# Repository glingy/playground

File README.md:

# Atmel SAM D21 Playground!

## Important Links
 * Documentation: WIP
 * How to make your own Playground: [docs/making_a_playground.md](./docs/making_a_playground.md)
 * BOM: https://playground.ctrtl.com/bom
 * Schematic: https://playground.ctrtl.com/schematic.pdf
 * ATSAMD21E15L Datasheet: https://playground.ctrtl.com/SAMD21.pdf
 * Latest Gerber Files: https://github.com/glingy/playground/releases/latest

This repository contains the development kit for building code for the Atmel SAM D21 playground board. This board was developed to help members of the Solar Car Club (Prisum) at Iowa State University to learn how to program very low level embedded code. This repository is a reduced version of the development environment used by the team.

### Getting Started
 - Download VS Code (https://code.visualstudio.com)
 - Install Git (`build-essential` package on Ubuntu, Run `xcode-select --install` in a terminal on macOS, or install from https://git-scm.com/downloads for Windows)
 - Clone this repository to your computer
 - Open the folder with VS Code (Either drag the folder onto the VS Code application or open VS Code and select `Open Folder...`)
 - VS Code will prompt you to install some recommended extensions. Do so, it should install PlatformIO, C/C++ tools, multisrc, and Explorer Exclude.
   - This environment is based on PlatformIO (https://platformio.org) with several modifications to make it easier to use.

### What is all this stuff?
 - Several of these are hidden by default, look in the `Hidden Items` tab in the explorer sidebar to see them. If it's hidden, you can ignore it for the most part.
 - `.vscode` - VSCode configuration. Suggested extensions, file type associations, configuration of what's hidden, etc.
 - `boards` - PlatformIO board definition for the playground board.
 - `include` - Shared header files across all projects (See PlatformIO documentation)
 - `lib` - Shared library code across all projects (See PlatformIO documentation)
 - `scripts` - Linker scripts and C startup files. You probably won't need to touch this, but feel free to explore
 - `sources` - The code folder! To create a new project, create a new folder in here. To be detected as a valid project, it must contain at least once `.c` file.
 - `.clang-format` - Auto-formatter config file. It's who you blame if your code magically reorganizes whenever you save the file.
 - `.gitignore` - Tells git to ignore specific files which should not be tracked.
 - `.multisrc` - Tells the multisrc extension to activate and allow you to select source folders.
 - `README.md` - This file!
 - `platformio.ini` - PlatformIO config file.
 - `multisrc.ini` - Generated PlatformIO config file by multisrc

### Bottom Status Bar Overview
PlatformIO adds a lot of buttons to the bottom status bar in VSCode. From left to right:
 - The first button is the checkmark, clicking that will build your code, but not run it. Good for checking syntax or verifying code when you don't have a board with you to run it on.
 - The second is the right arrow, that's the run button. It will build and run your code using the selected debugger.
 - The third is the trash can, that will delete everything from the build folder. If there's a strange linker error for some reason, you can try cleaning, but I've found that it's usually your fault and not because the build folder is dirty.
 - The serial monitor (plug) is not used yet.
 - The terminal will open a local terminal window with the `pio` command set up for debugging the development environment.
 - The next is the selected debugger. By default, it will assume the playground's internal debugger, but you can select another in `local.ini`. See `platform.ini` for example debugger definitions.
 - When editing, you may see a database icon and/or a fire symbol to the left of the line and column numbers. That indicates that intellisense is parsing the file, so if syntax highlighting or linting looks broken, wait for those to disappear, and if it's not fixed by the time they disappear, close and reopen the file.
 - In the bottom right corner of VSCode, `< something >` indicates the source folder currently selected for running / debugging. It will be red if you're looking at a file not in the current project so you don't compile the wrong project on accident. Click that to select a different project

### Running
 - Select the program. Select the debugger. Press the arrow.

### Debugging
 - On the left sidebar, there's a bug with a play button, press the green arrow at the top of that sidebar to debug.
   - `Variables` are the global (and local) variables that were not optimized away. You can also hover over a variable to see its value. If it says `<optimized away>`, the compiler decided that variable wasn't worth keeping around, so you'll have to either declare it `volatile` and re-download (forces compiler to not optimize it out; remove `volatile` when done) or look around to find its value from nearby functions or calculations.
   - `Watch` lets you type C expressions and see the results. This is extremely useful also for optimized math, you can put any simple C expression (including math) in there, `&var` or `&var + len` is often useful for checking addresses of different things.
   - `Call Stack` shows which functions you're currently inside. If you go above `main`, you're now in the `scripts/startup.c` file. Click on an entry to jump to that function.
   - `Peripherals` shows the current status of every register in the processor. Extremely useful, especially if something's just broken and you have no idea why. Sometimes, register values won't update unless you click on them to expand them, if you see it flash or a loading bar at the top flash by, it probably just updated. Most useful part of debugging.
   - `Breakpoints` is self-explanatory. Click next to a line number to add a breakpoint. Note: Breakpoints listed there are for *all* projects, not just the current one, so it might be useful to remove breakpoints as soon as you're done with one.
   - `Registers` is not very useful for us, it's the current value of every register in the processor.
   - `Memory` enter a memory address and offset to see the hex value of that chunk of memory.
   - `Disassembly` if it works, it will disassemble a function to let you see the assembly form it is currently running. I've had issues with that in the past.
 - You can press the run button or the debug button again while debugging the program, different debuggers behave differently, some get angry, some stop the current debug process while making vscode think you're still debugging, some just ignore you. I suggest you press the stop debugging button before starting a new program.
 - The reload button will restart the current program, but *will not recompile nor re-download*. If you want to download a new version, stop and restart.

### Troubleshooting
**Help!** LED doesn't turn on!
 - Check wiring direction of external pullup/pulldown resistors (0/1)
 - Check output direction

**Help!** A peripheral isn't working!
 - Is it enabled in APB? - Did you wait after enabling it for the clock to enable?
 - Does it need AHB enabled?
 - Is it enabled?
 - Is its GCLK enabled?

**Help!** I need to force wipe and reset the board!
 - TBD

**Help!** It's just not working!
 - Yup. Welcome to software. Take a break and come back later. The answer's probably staring you in the face.

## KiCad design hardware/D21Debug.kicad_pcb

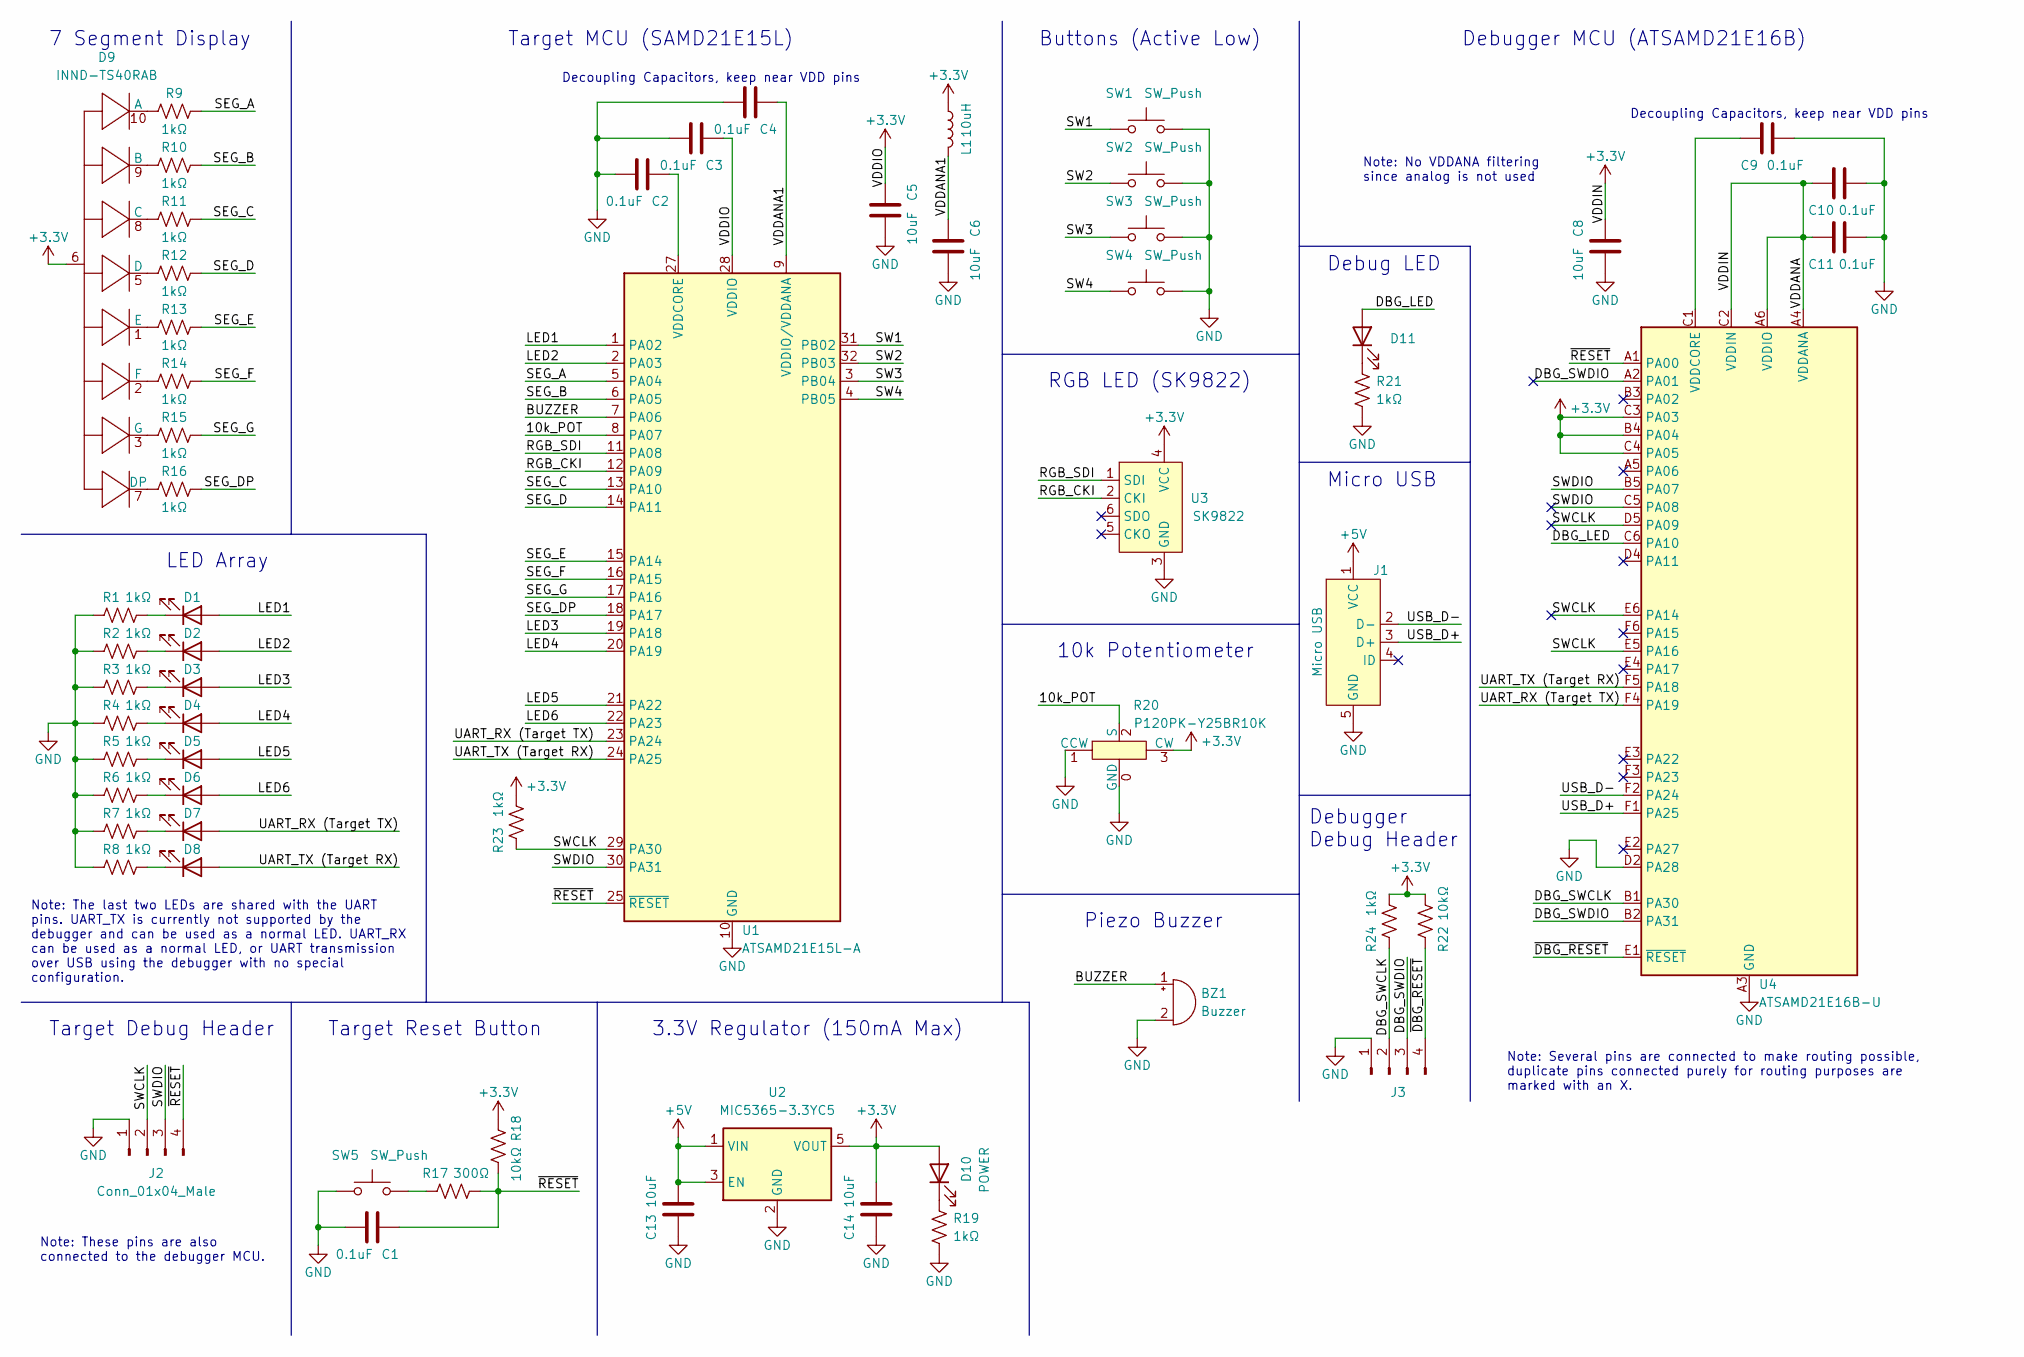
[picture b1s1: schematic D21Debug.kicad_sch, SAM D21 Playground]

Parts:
BZ1: Buzzer; PS1240P02BT
C1, C2, C3, C4, C9, C10, C11: 0.1uF; C_0603_1608Metric_Pad1.08x0.95mm_HandSolder
C5, C6, C8, C13, C14: 10uF; C_0603_1608Metric_Pad1.08x0.95mm_HandSolder
D1, D2, D3, D4, D5, D6, D7, D8, D11: LED_0603_1608Metric_Pad1.05x0.95mm_HandSolder
D9: INND-TS40RAB
D10: POWER; LED_0603_1608Metric_Pad1.05x0.95mm_HandSolder
J1: Micro USB; MCR-B-S-RA-SMT-CS5A-NF-T
J2, J3: Conn_01x04_Male; PinHeader_1x04_P2.54mm_Vertical
L1: 10uH; L_0603_1608Metric_Pad1.05x0.95mm_HandSolder
R1, R2, R3, R4, R5, R6, R7, R8, R9, R10, R11, R12, R13, R14, R15, R16, R19, R21, R23, R24: 1kΩ; R_0603_1608Metric_Pad0.98x0.95mm_HandSolder
R17: 300Ω; R_0603_1608Metric_Pad0.98x0.95mm_HandSolder
R18, R22: 10kΩ; R_0603_1608Metric_Pad0.98x0.95mm_HandSolder
R20: P120PK-Y25BR10K
SW1, SW2, SW3, SW4, SW5: SW_Push; SW_PUSH_6mm
U1: ATSAMD21E15L-A; TQFP-32_7x7mm_P0.8mm
U2: MIC5365-3.3YC5; SOT-353_SC-70-5
U3: SK9822
U4: ATSAMD21E16B-U; WLCSP-35

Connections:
+3V3: C3.1, C5.1, C8.1, C10.1, C11.1, C14.2, D9.6, D10.2 (A), L1.2, R18.1, R20.3 (CW), R22.1, R23.2, R24.2, U1.28 (VDDIO), U2.5 (VOUT), U3.4 (VCC), U4.A4 (VDDANA), U4.A6 (VDDIO), U4.B4 (PA04), U4.C2 (VDDIN), U4.C3 (PA03), U4.C4 (PA05)
+5V: C13.2, J1.1 (VCC), U2.1 (VIN), U2.3 (EN)
/10k_POT: R20.2 (S), U1.8 (PA07)
/BUZZER: BZ1.1 (-), U1.7 (PA06)
/DBG_LED: D11.2 (A), U4.C6 (PA10)
/DBG_SWCLK: J3.2, R24.1, U4.B1 (PA30)
/DBG_SWDIO: J3.3, U4.A2 (PA01), U4.B2 (PA31)
/LED1: D1.2 (A), U1.1 (PA02)
/LED2: D2.2 (A), U1.2 (PA03)
/LED3: D3.2 (A), U1.19 (PA18)
/LED4: D4.2 (A), U1.20 (PA19)
/LED5: D5.2 (A), U1.21 (PA22)
/LED6: D6.2 (A), U1.22 (PA23)
/RGB_CKI: U1.12 (PA09), U3.2 (CKI)
/RGB_SDI: U1.11 (PA08), U3.1 (SDI)
/SEG_A: R9.2, U1.5 (PA04)
/SEG_B: R10.2, U1.6 (PA05)
/SEG_C: R11.2, U1.13 (PA10)
/SEG_D: R12.2, U1.14 (PA11)
/SEG_DP: R16.2, U1.18 (PA17)
/SEG_E: R13.2, U1.15 (PA14)
/SEG_F: R14.2, U1.16 (PA15)
/SEG_G: R15.2, U1.17 (PA16)
/SW1: SW1.1, U1.31 (PB02); also elsewhere on the board
/SW2: SW2.1, U1.32 (PB03); also elsewhere on the board
/SW3: SW3.1, U1.3 (PB04)
/SW4: SW4.1, U1.4 (PB05)
/SWCLK: J2.2, R23.1, U1.29 (PA30), U4.D5 (PA09), U4.E5 (PA16), U4.E6 (PA14)
/SWDIO: J2.3, U1.30 (PA31), U4.B5 (PA07), U4.C5 (PA08)
/UART_RX (Target TX): D7.2 (A), U1.23 (PA24), U4.F4 (PA19)
/UART_TX (Target RX): D8.2 (A), U1.24 (PA25), U4.F5 (PA18)
/USB_D+: J1.3 (D+), U4.F1 (PA25)
/USB_D-: J1.2 (D-), U4.F2 (PA24)
/VDDANA1: C4.1, C6.1, L1.1, U1.9 (VDDIO/VDDANA)
/~DBG_RESET: J3.4, R22.2, U4.E1 (~RESET)
/~RESET: C1.1, J2.4, R17.2, R18.2, U1.25 (~RESET), U4.A1 (PA00)
GND: BZ1.2 (+), C1.2, C2.2, C3.2, C4.2, C5.2, C6.2, C8.2, C9.2, C10.2, C11.2, C13.1, C14.1, J1.5 (GND), J2.1, J3.1, R1.1, R2.1, R3.1, R4.1, R5.1, R6.1, R7.1, R8.1, R19.2, R20.0 (GND), R20.1 (CCW), R21.2, SW1.2, SW2.2, SW3.2, SW4.2, SW5.1, U1.10 (GND), U1.26 (GND), U2.2 (GND), U3.3 (GND), U4.A3 (GND), U4.D2 (PA28), U4.G (GND); also elsewhere on the board
unnamed: D1.1 (K), R1.2
unnamed: D2.1 (K), R2.2
unnamed: D3.1 (K), R3.2
unnamed: D4.1 (K), R4.2
unnamed: D5.1 (K), R5.2
unnamed: D6.1 (K), R6.2
unnamed: D7.1 (K), R7.2
unnamed: D8.1 (K), R8.2
unnamed: D9.10 (A), R9.1
unnamed: D9.9 (B), R10.1
unnamed: D9.8 (C), R11.1
unnamed: D9.5 (D), R12.1
unnamed: D9.7 (DP), R16.1
unnamed: D9.1 (E), R13.1
unnamed: D9.2 (F), R14.1
unnamed: D9.3 (G), R15.1
unnamed: D10.1 (K), R19.1
unnamed: D11.1 (K), R21.1
unnamed: R17.1, SW5.2
unnamed: C2.1, U1.27 (VDDCORE)
unnamed: C9.1, U4.C1 (VDDCORE)

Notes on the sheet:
3.3V Regulator (150mA Max)
Target MCU (SAMD21E15L)
Note: The last two LEDs are shared with the UART pins. UART_TX is currently not supported by the debugger and can be used as a normal LED. UART_RX can be used as a normal LED, or UART transmission over USB using the debugger with no special configuration.
Note: Several pins are connected to make routing possible, duplicate pins connected purely for routing purposes are marked with an X.
Micro USB
Debugger MCU (ATSAMD21E16B)
Target Debug Header
Decoupling Capacitors, keep near VDD pins
Debug LED
LED Array
Piezo Buzzer
Debugger Debug Header
RGB LED (SK9822)
Note: These pins are also connected to the debugger MCU.
10k Potentiometer
Buttons (Active Low)
7 Segment Display
Target Reset Button
Note: No VDDANA filtering since analog is not used

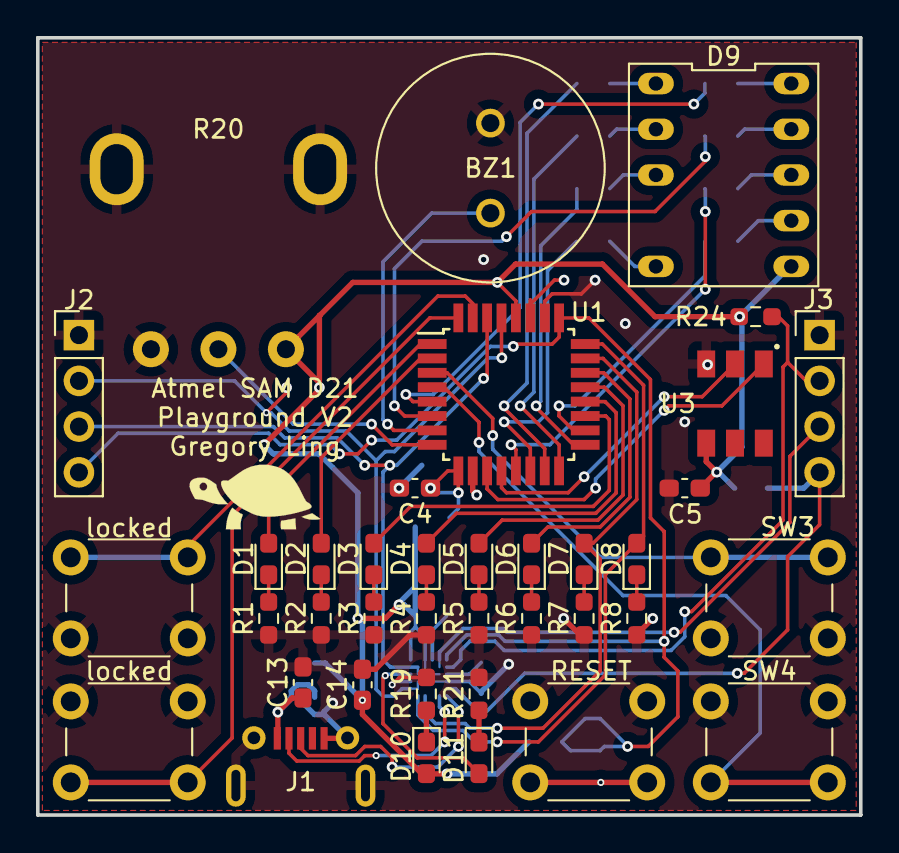
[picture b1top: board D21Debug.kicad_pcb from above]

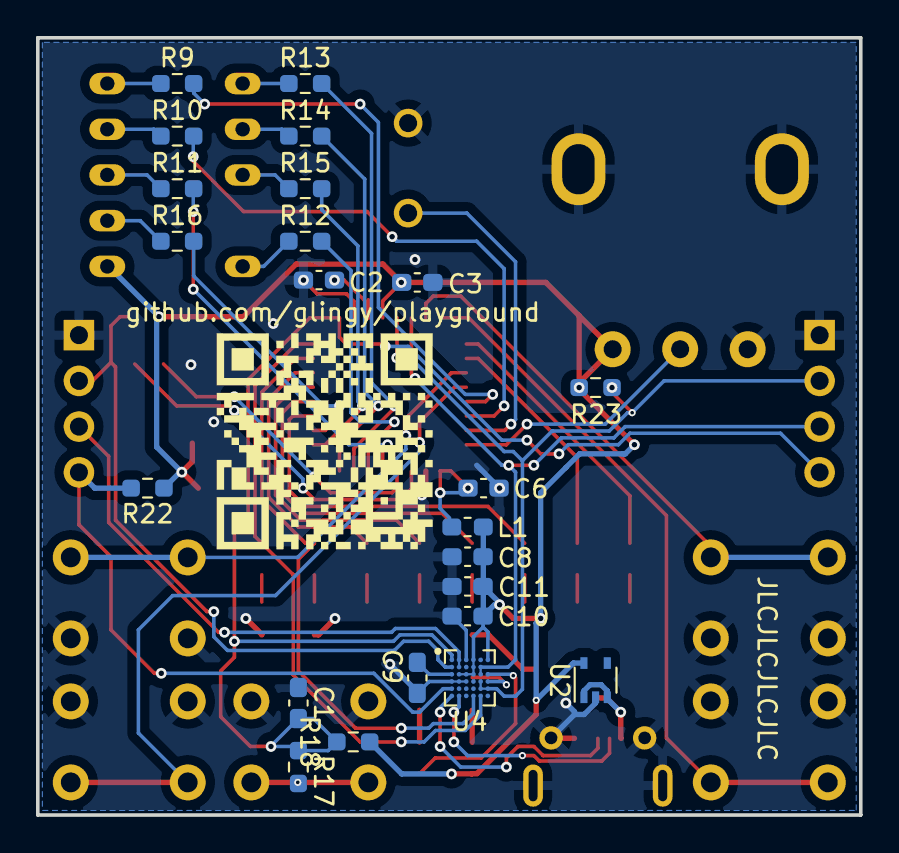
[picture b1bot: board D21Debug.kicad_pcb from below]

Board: 2 copper layers, 45.7 x 43.2 mm, 61 parts (23 on the bottom side), 58 nets.

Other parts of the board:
locked: SW_Push; SW_PUSH_6mm
locked#2: SW_Push; SW_PUSH_6mm

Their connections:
/SW1: locked.1; also elsewhere on the board
/SW2: locked#2.1; also elsewhere on the board
GND: locked.2, locked#2.2; also elsewhere on the board

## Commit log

2023-01-25 Added docs
2023-01-25 Create CNAME
2023-01-25 Fix GH pages for static site
2023-01-25 Updated some 1ks
2023-01-25 Didn't export right
2023-01-27 Removed .DS_Store
2023-01-27 updated bom
2023-02-04 Added KiCAD project
2023-02-04 Fixed schematic
2023-02-22 Cleaned up schematic and BOM
2023-02-22 Forgot to save PCB
2023-03-03 Fix gitignore
2023-03-03 Added development environment
2023-03-03 Fixed list
2024-09-02 Fix reset line in schematic
2024-11-18 Add building a playground docs
    - Ordering parts
    - Putting together the hardware
    - Programming the debugger
    - Testing the board
